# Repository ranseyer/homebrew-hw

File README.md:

View this project on [CADLAB.io](https://cadlab.io/project/22743). 

# homebrew-hw

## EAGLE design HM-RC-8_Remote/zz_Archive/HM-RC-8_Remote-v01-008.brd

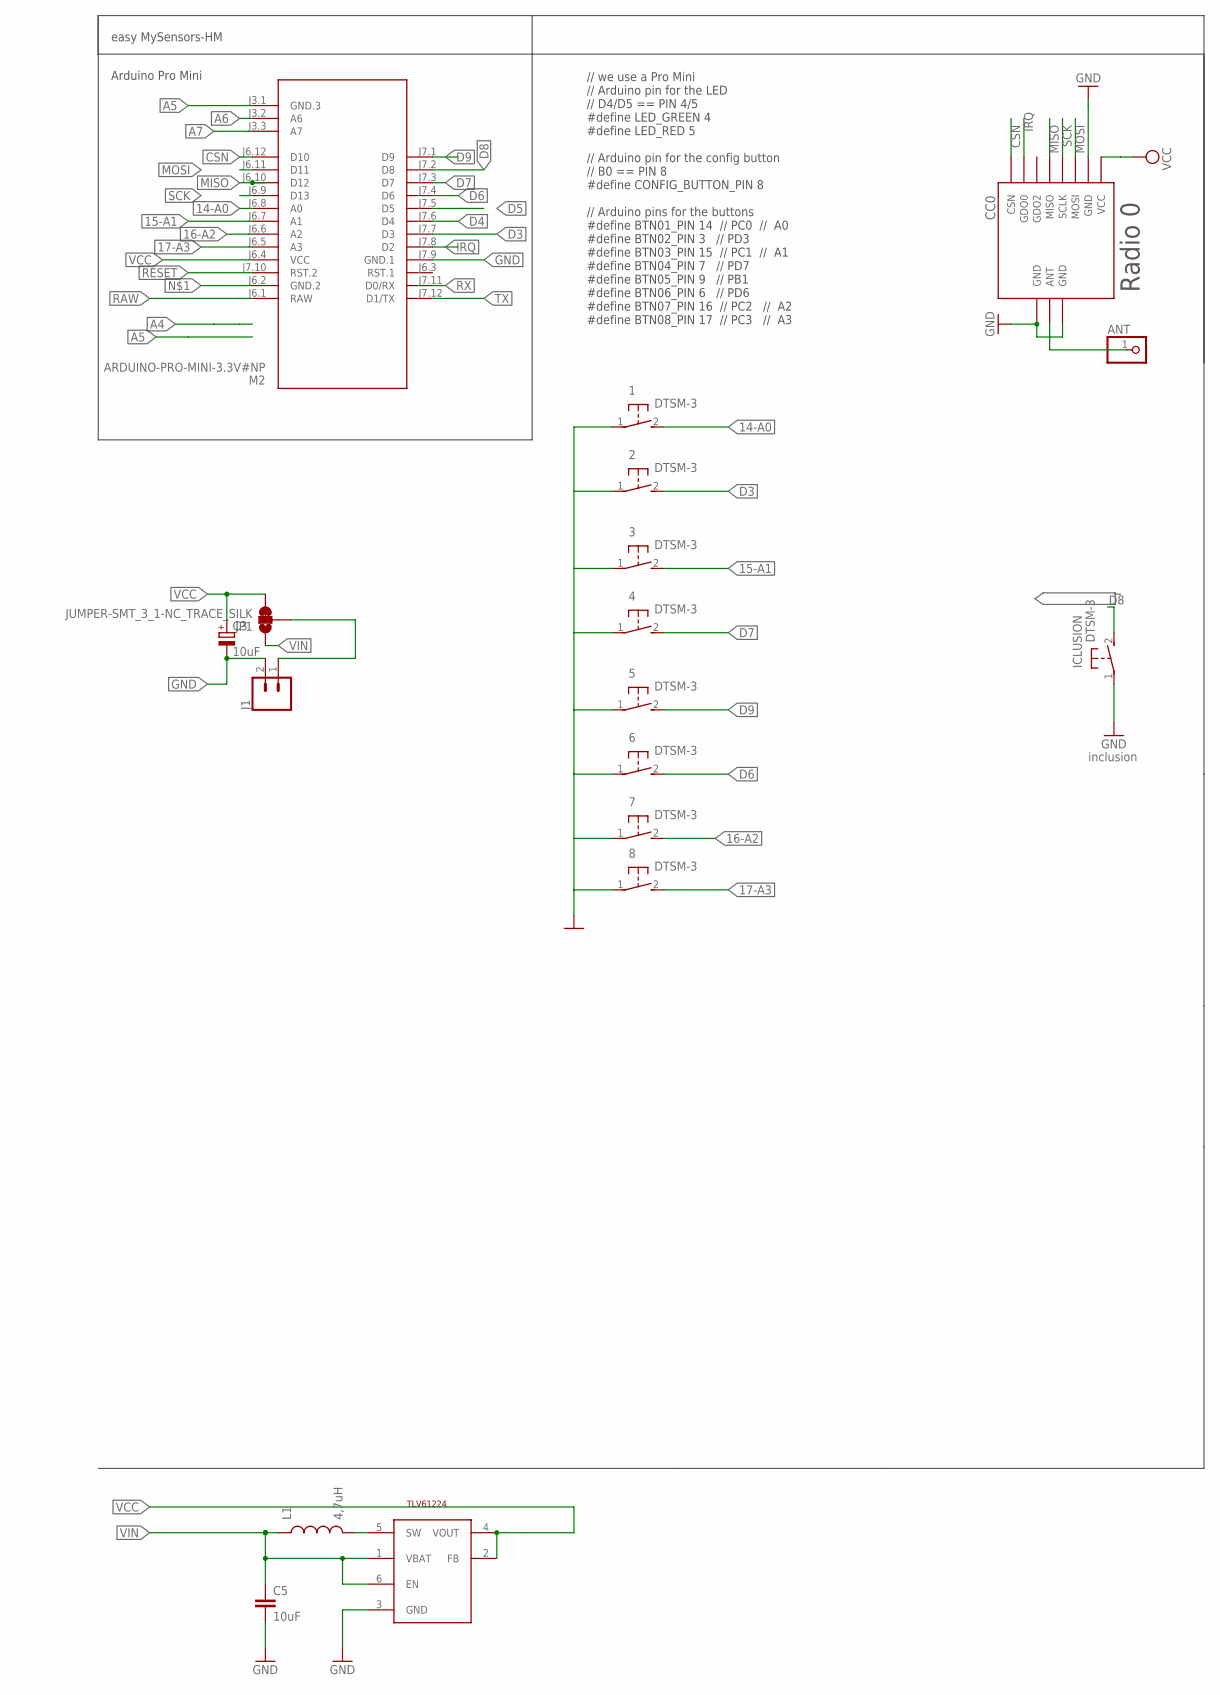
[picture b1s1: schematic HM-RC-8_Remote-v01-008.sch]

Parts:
1, 2, 3, 4, 5, 6, 7, 8: DTSM-3
ANT: PINHD-1X1; 1X01
C3: 10uF; SMC_C
C5: 10uF; 0805
CC0: CC1101; CC1101_MODULE1_SMD
ICLUSION: DTSM-3
J1: CONN_02PTH3; 1X02_LONGPADS
JP1: JUMPER-SMT_3_1-NC_TRACE_SILK; SMT-JUMPER_3_1-NC_TRACE_SILK
L1: 4,7uH; 0805
M2: ARDUINO-PRO-MINI-3.3V#NP; ARDUINO-PRO-MINI#NP
STEPUP: TLV61224; SOT23-6L

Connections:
14-A0: 1.2, M2.J6.8 (A0)
15-A1: 3.2, M2.J6.7 (A1)
16-A2: 7.2, M2.J6.6 (A2)
17-A3: 8.2, M2.J6.5 (A3)
A5: M2.J3.1 (GND.3)
A6: M2.J3.2 (A6)
A7: M2.J3.3 (A7)
ANT0: ANT.1, CC0.ANT
CSN: CC0.CSN, M2.J6.12 (D10)
D3: 2.2, M2.J7.7 (D3)
D4: M2.J7.6 (D4)
D5: M2.J7.5 (D5)
D6: 6.2, M2.J7.4 (D6)
D7: 4.2, M2.J7.3 (D7)
D8: ICLUSION.2, M2.J7.2 (D8)
D9: 5.2, M2.J7.1 (D9)
GND: 1.1, 3.1, 4.1, 5.1, 6.1, 7.1, 8.1, C3.-, C5.2, CC0.GND@0 (GND), CC0.GND@1 (GND), CC0.GND@2 (GND), ICLUSION.1, J1.2, M2.J7.9 (GND.1), STEPUP.3 (GND)
IRQ: CC0.GDO0, M2.J7.8 (D2)
MISO: CC0.MISO, M2.J6.10 (D12)
MOSI: CC0.MOSI, M2.J6.11 (D11)
unnamed: J1.1, JP1.2
unnamed: L1.2, STEPUP.5 (SW)
RAW: M2.J6.1 (RAW)
RESET: M2.J7.10 (RST.2)
RX: M2.J7.11 (D0/RX)
SCK: CC0.SCLK, M2.J6.9 (D13)
TX: M2.J7.12 (D1/TX)
VCC: C3.+, CC0.VCC, JP1.3, M2.J6.4 (VCC), STEPUP.2 (FB), STEPUP.4 (VOUT)
VIN: C5.1, JP1.1, L1.1, STEPUP.1 (VBAT), STEPUP.6 (EN)

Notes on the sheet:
easy MySensors-HM
Arduino Pro Mini
Radio 0
inclusion
// we use a Pro Mini // Arduino pin for the LED // D4/D5 == PIN 4/5 #define LED_GREEN 4 #define LED_RED 5 // Arduino pin for the config button // B0 == PIN 8 #define CONFIG_BUTTON_PIN 8 // Arduino pins for the buttons #define BTN01_PIN 14 // PC0 // A0 #define BTN02_PIN 3 // PD3 #define BTN03_PIN 15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

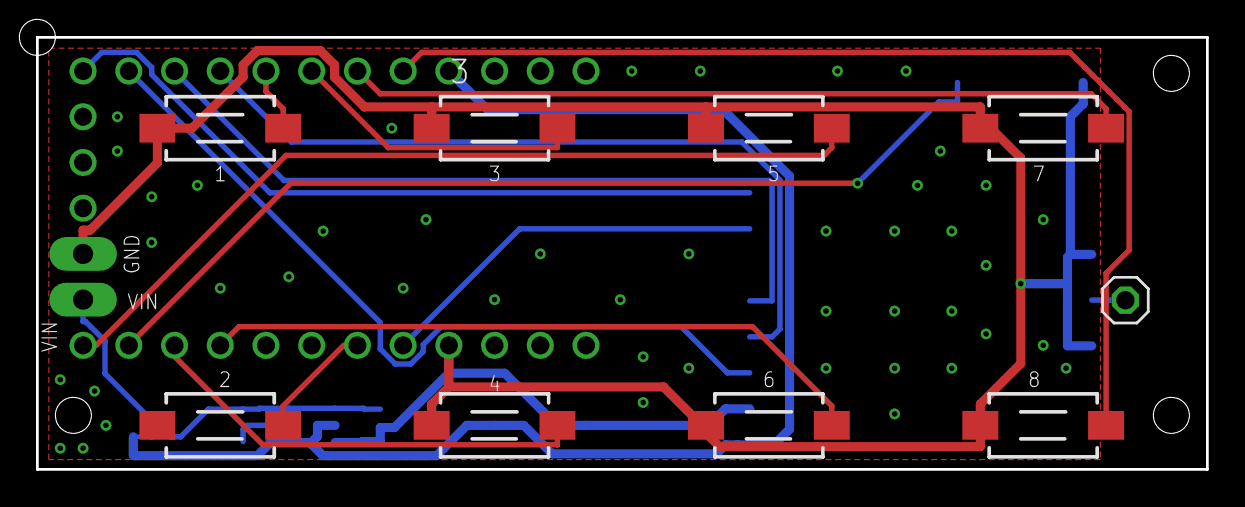
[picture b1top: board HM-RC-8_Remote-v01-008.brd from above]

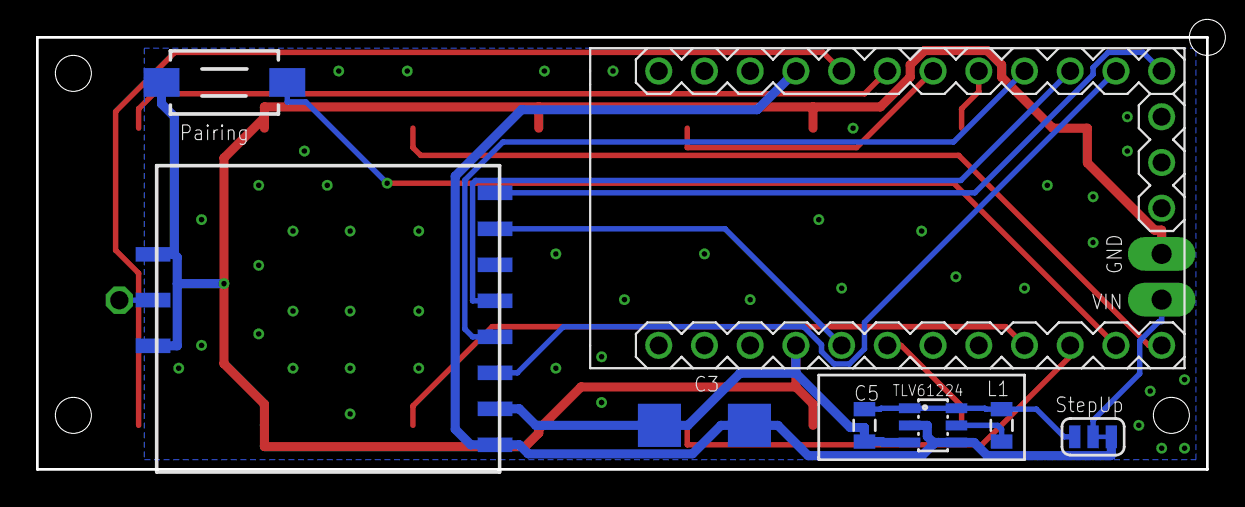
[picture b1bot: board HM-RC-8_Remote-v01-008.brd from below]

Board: 2 copper layers, 65.0 x 24.0 mm, 18 parts (8 on the bottom side), 20 nets.

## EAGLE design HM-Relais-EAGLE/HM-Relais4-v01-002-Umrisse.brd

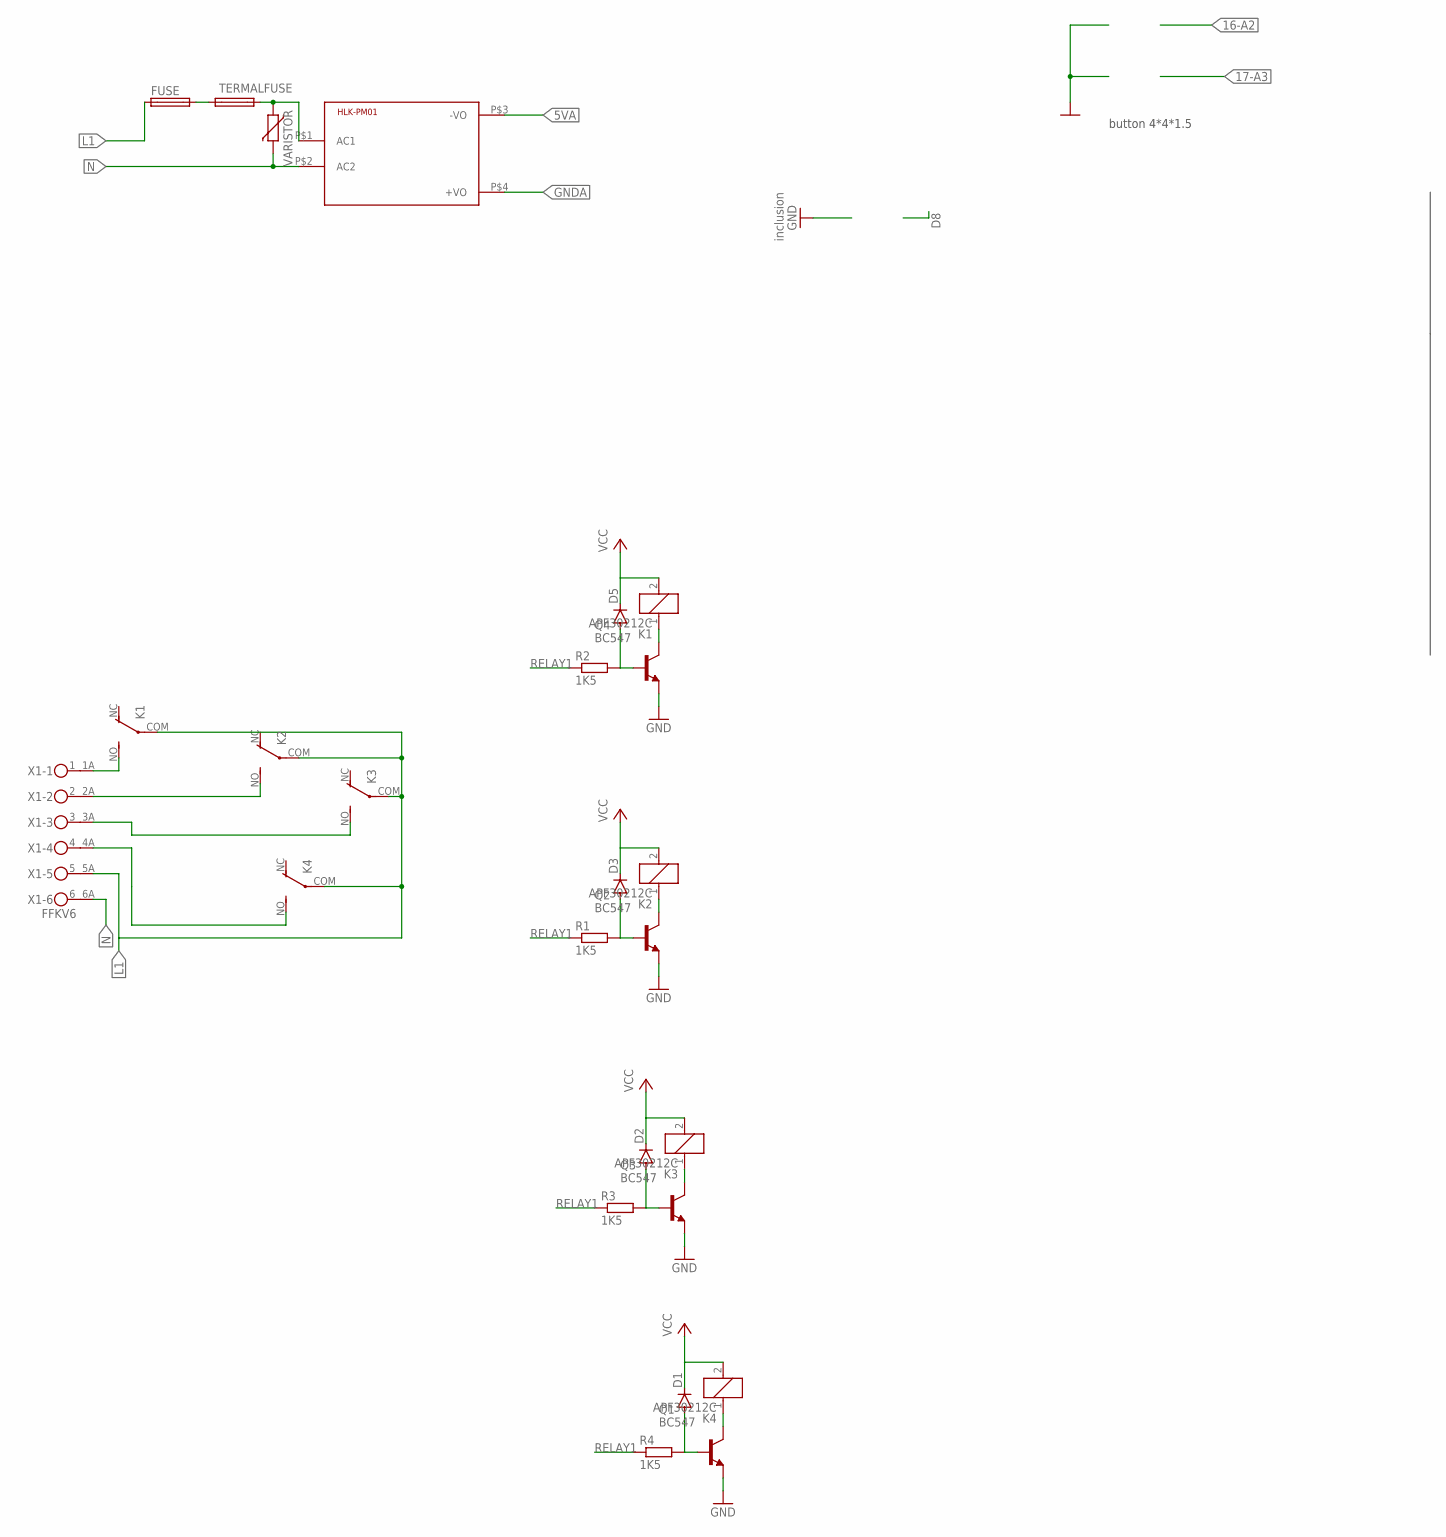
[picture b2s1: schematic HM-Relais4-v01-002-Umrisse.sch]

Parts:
D1, D2, D3, D5: DIODE-D-2.5; D-2.5
FUSE: FUSETE5; TE5
HLK-PM01: HKLPM01
K1, K2, K3, K4: APF30212C
Q1, Q2, Q3, Q4: BC547; TO92
R1, R2, R3, R4: 1K5; 0207/2V
TERMALFUSE: FUSETE5; TE5
VARISTOR: VARISTOR-7,5; R-7,5
X1: FFKV6

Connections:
5VA: HLK-PM01.P$3 (-VO)
GND: Q1.1 (E), Q2.1 (E), Q3.1 (E), Q4.1 (E)
GNDA: HLK-PM01.P$4 (+VO)
L1: FUSE.1, K1.COM, K2.COM, K3.COM, K4.COM, X1.5A (2)
N: HLK-PM01.P$2 (AC2), VARISTOR.2, X1.6A (2)
unnamed: FUSE.2, TERMALFUSE.2
unnamed: K2.1, Q2.3 (C)
unnamed: D3.A, Q2.2 (B), R1.2
unnamed: K3.1, Q3.3 (C)
unnamed: D2.A, Q3.2 (B), R3.2
unnamed: HLK-PM01.P$1 (AC1), TERMALFUSE.1, VARISTOR.1
unnamed: K4.1, Q1.3 (C)
unnamed: D1.A, Q1.2 (B), R4.2
unnamed: K1.NO (S), X1.1A (2)
unnamed: K2.NO (S), X1.2A (2)
unnamed: K3.NO (S), X1.3A (2)
unnamed: K1.1, Q4.3 (C)
unnamed: K4.NO (S), X1.4A (2)
unnamed: D5.A, Q4.2 (B), R2.2
RELAY1: R1.1, R2.1, R3.1, R4.1
VCC: D1.C, D2.C, D3.C, D5.C, K1.2, K2.2, K3.2, K4.2

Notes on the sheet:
inclusion
button 4*4*1.5

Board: 2 copper layers, 21 parts (0 on the bottom side), 19 nets, no tracks yet.

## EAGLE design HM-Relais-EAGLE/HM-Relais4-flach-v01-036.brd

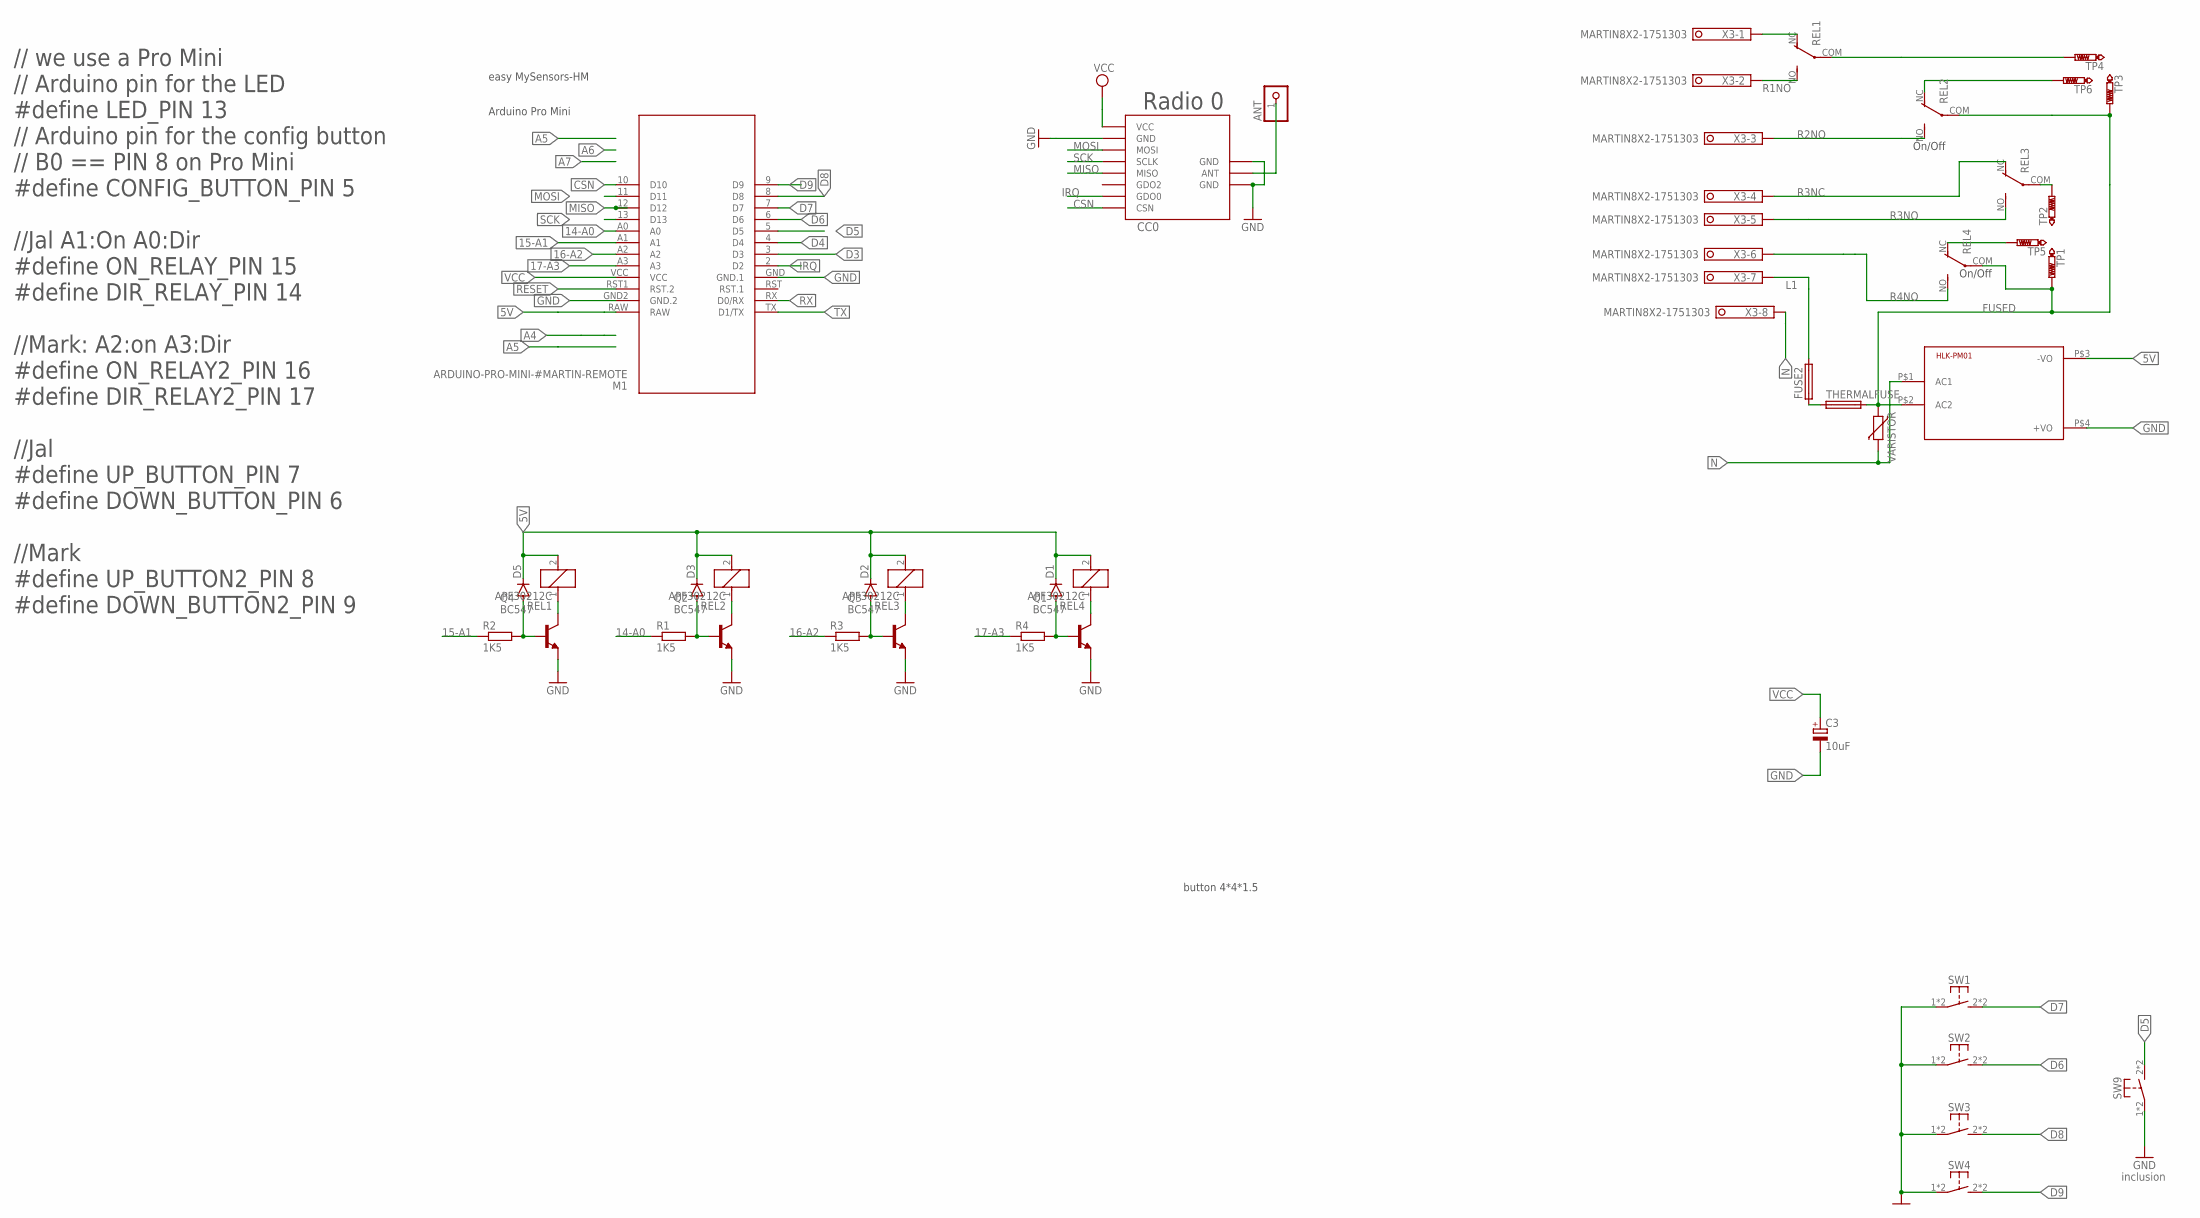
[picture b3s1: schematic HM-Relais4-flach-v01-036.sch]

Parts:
ANT: PINHD-1X1; 1X01
C3: 10uF; SMC_C
CC0: CC1101; CC1101_MODULE1_SMD
D1, D2, D3, D5: DIODE-D-2.5; D-2.5
FUSE2: FUSETE5; TE5
HLK-PM01: HKLPM01
M1: ARDUINO-PRO-MINI-#MARTIN-REMOTE; ARDUINO-PRO-MINI#NP-MARTIN-REMOTE
Q1, Q2, Q3, Q4: BC547; TO92
R1, R2, R3, R4: 1K5; 0207/2V
REL1, REL2, REL3, REL4: APF30212C
SW1, SW2, SW3, SW4, SW9: SW-TACTILE-TL3305; TL3305
THERMALFUSE: FUSETE5; TE5
TP1, TP2, TP3, TP4, TP5, TP6: PTR1TP11SQ; TP11SQ
VARISTOR: VARISTOR-7,5; R-7,5
X3: MARTIN8X2-1751303; 1751303

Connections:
5V: D1.C, D2.C, D3.C, D5.C, HLK-PM01.P$3 (-VO), M1.RAW, REL1.2, REL2.2, REL3.2, REL4.2
14-A0: M1.A0, R1.1
15-A1: M1.A1, R2.1
16-A2: M1.A2, R3.1
17-A3: M1.A3, R4.1
ANT0: ANT.1, CC0.ANT
CSN: CC0.CSN, M1.10 (D10)
D3: M1.3 (D3)
D4: M1.4 (D4)
D5: M1.5 (D5), SW9.2 (S1), SW9.3 (S1)
D6: M1.6 (D6), SW2.2 (S1), SW2.3 (S1)
D7: M1.7 (D7), SW1.2 (S1), SW1.3 (S1)
D8: M1.8 (D8), SW3.2 (S1), SW3.3 (S1)
D9: M1.9 (D9), SW4.2 (S1), SW4.3 (S1)
FUSED: HLK-PM01.P$2 (AC2), REL2.COM, REL4.COM, THERMALFUSE.2, TP1.TP, TP3.TP, VARISTOR.1
GND: C3.-, CC0.GND@0 (GND), CC0.GND@1 (GND), CC0.GND@2 (GND), HLK-PM01.P$4 (+VO), M1.GND (GND.1), M1.GND2 (GND.2), Q1.1 (E), Q2.1 (E), Q3.1 (E), Q4.1 (E), SW1.1, SW1.4 (P1), SW2.1, SW2.4 (P1), SW3.1, SW3.4 (P1), SW4.1, SW4.4 (P1), SW9.1, SW9.4 (P1)
IRQ: CC0.GDO0, M1.2 (D2)
L1: FUSE2.2, X3.15
MISO: CC0.MISO, M1.12 (D12)
MOSI: CC0.MOSI, M1.11 (D11)
N: HLK-PM01.P$1 (AC1), VARISTOR.2, X3.16
unnamed: FUSE2.1, THERMALFUSE.1
unnamed: Q2.3 (C), REL2.1
unnamed: D3.A, Q2.2 (B), R1.2
unnamed: REL3.COM, TP2.TP
unnamed: Q3.3 (C), REL3.1
unnamed: D2.A, Q3.2 (B), R3.2
unnamed: REL4.NC (O), TP5.TP
unnamed: Q1.3 (C), REL4.1
unnamed: D1.A, Q1.2 (B), R4.2
unnamed: REL1.COM, TP4.TP
unnamed: REL2.NC (O), TP6.TP
unnamed: Q4.3 (C), REL1.1
unnamed: D5.A, Q4.2 (B), R2.2
R1NC: REL1.NC (O), X3.9
R1NO: REL1.NO (S), X3.10
R2NO: REL2.NO (S), X3.11
R3NC: REL3.NC (O), X3.12
R3NO: REL3.NO (S), X3.13
R4NO: REL4.NO (S), X3.14
RESET: M1.RST1 (RST.2)
RX: M1.RX (D0/RX)
SCK: CC0.SCLK, M1.13 (D13)
TX: M1.TX (D1/TX)
VCC: C3.+, CC0.VCC, M1.VCC

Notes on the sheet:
easy MySensors-HM
Arduino Pro Mini
Radio 0
inclusion
button 4*4*1.5
// we use a Pro Mini // Arduino pin for the LED #define LED_PIN 13 // Arduino pin for the config button // B0 == PIN 8 on Pro Mini #define CONFIG_BUTTON_PIN 5 //Jal A1:On A0:Dir #define ON_RELAY_PIN 15 #define DIR_RELAY_PIN 14 //Mark: A2:on A3:Dir #define ON_RELAY2_PIN 16 #define DIR_RELAY2_PIN 17 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
On/Off

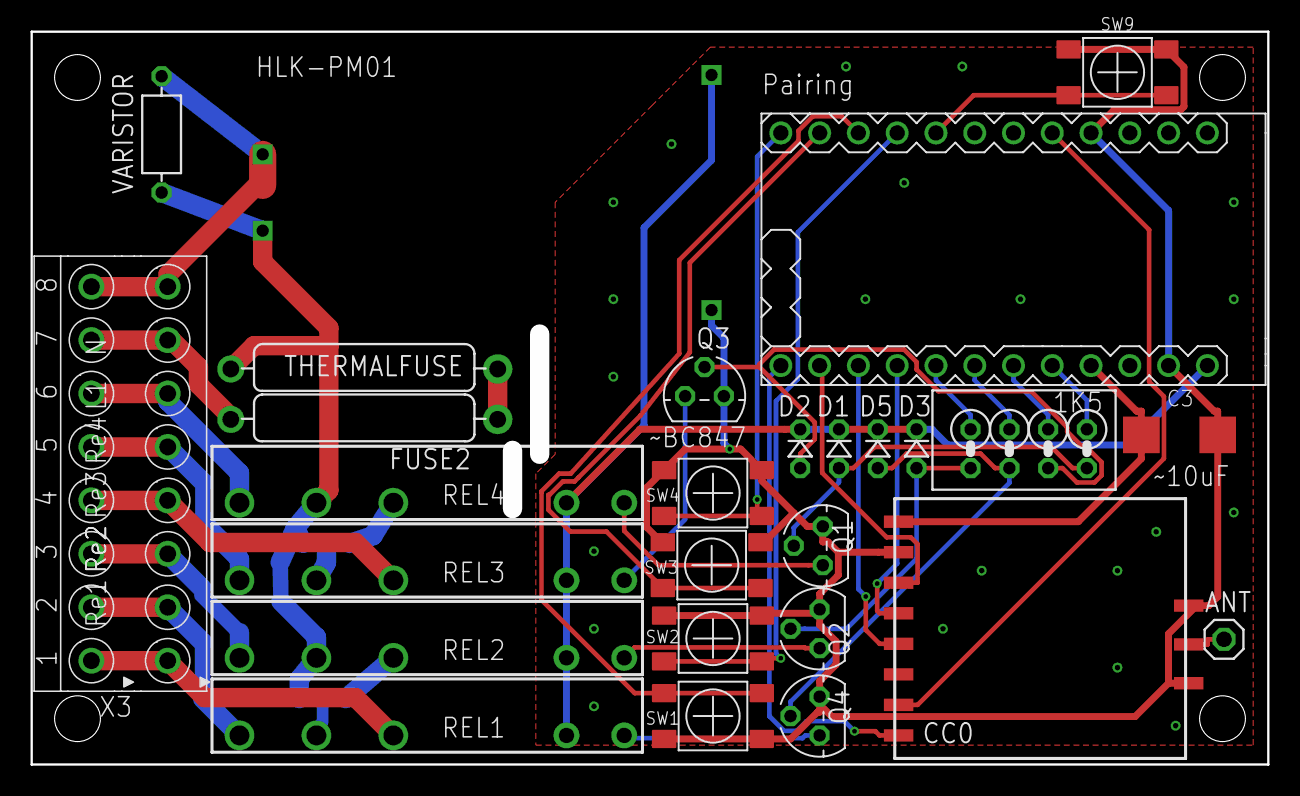
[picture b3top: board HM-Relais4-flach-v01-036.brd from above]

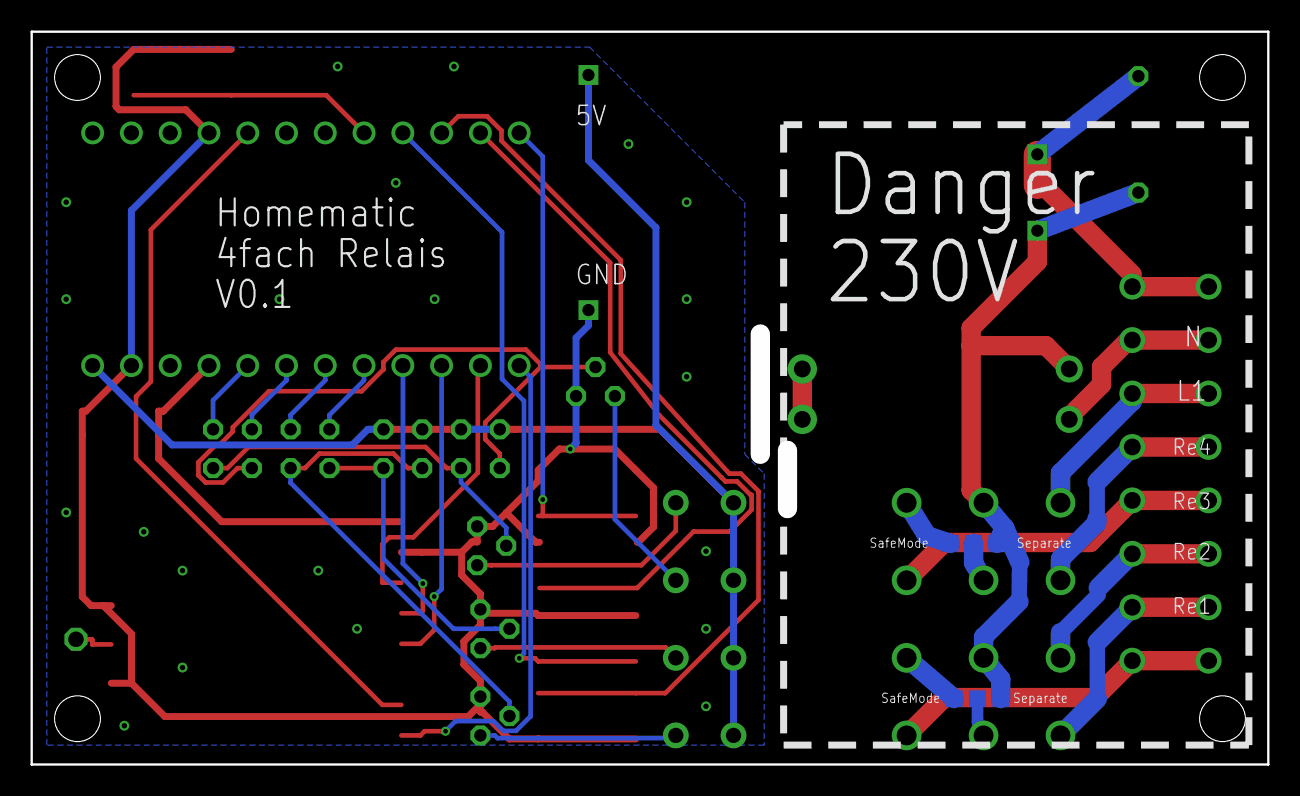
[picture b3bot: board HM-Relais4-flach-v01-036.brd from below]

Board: 2 copper layers, 79.9 x 46.9 mm, 36 parts (6 on the bottom side), 40 nets.

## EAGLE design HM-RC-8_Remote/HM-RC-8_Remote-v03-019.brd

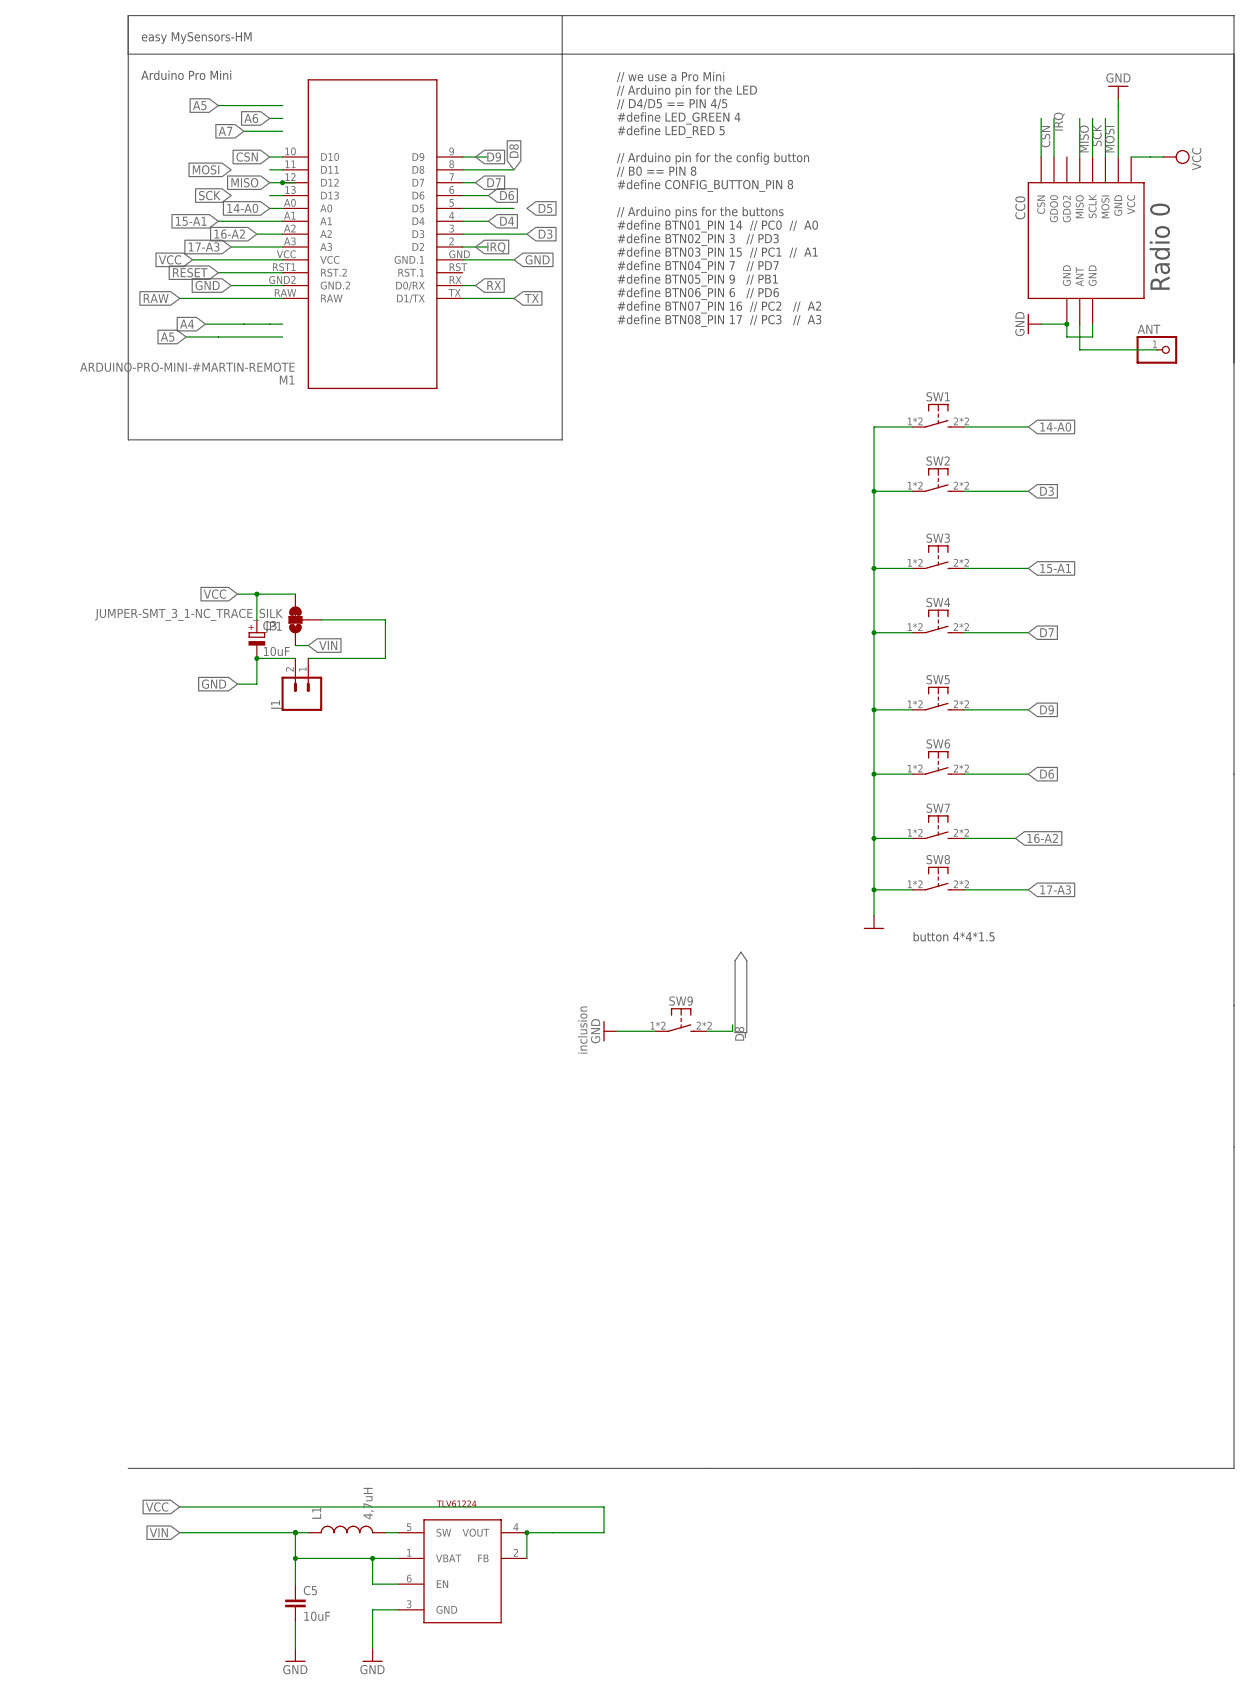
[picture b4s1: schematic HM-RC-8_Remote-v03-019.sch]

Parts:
ANT: PINHD-1X1; 1X01
C3: 10uF; SMC_C
C5: 10uF; 0805
CC0: CC1101; CC1101_MODULE1_SMD
J1: CONN_02PTH3; 1X02_LONGPADS
JP1: JUMPER-SMT_3_1-NC_TRACE_SILK; SMT-JUMPER_3_1-NC_TRACE_SILK
L1: 4,7uH; 0805
M1: ARDUINO-PRO-MINI-#MARTIN-REMOTE; ARDUINO-PRO-MINI#NP-MARTIN-REMOTE
STEPUP: TLV61224; SOT23-6L
SW1, SW2, SW3, SW4, SW5, SW6, SW7, SW8, SW9: SW-TACTILE-TL3305; TL3305

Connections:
14-A0: M1.A0, SW1.2 (S1), SW1.3 (S1)
15-A1: M1.A1, SW3.2 (S1), SW3.3 (S1)
16-A2: M1.A2, SW7.2 (S1), SW7.3 (S1)
17-A3: M1.A3, SW8.2 (S1), SW8.3 (S1)
ANT0: ANT.1, CC0.ANT
CSN: CC0.CSN, M1.10 (D10)
D3: M1.3 (D3), SW2.2 (S1), SW2.3 (S1)
D4: M1.4 (D4)
D5: M1.5 (D5)
D6: M1.6 (D6), SW6.2 (S1), SW6.3 (S1)
D7: M1.7 (D7), SW4.2 (S1), SW4.3 (S1)
D8: M1.8 (D8), SW9.2 (S1), SW9.3 (S1)
D9: M1.9 (D9), SW5.2 (S1), SW5.3 (S1)
GND: C3.-, C5.2, CC0.GND@0 (GND), CC0.GND@1 (GND), CC0.GND@2 (GND), J1.2, M1.GND (GND.1), M1.GND2 (GND.2), STEPUP.3 (GND), SW1.1, SW1.4 (P1), SW2.1, SW2.4 (P1), SW3.1, SW3.4 (P1), SW4.1, SW4.4 (P1), SW5.1, SW5.4 (P1), SW6.1, SW6.4 (P1), SW7.1, SW7.4 (P1), SW8.1, SW8.4 (P1), SW9.1, SW9.4 (P1)
IRQ: CC0.GDO0, M1.2 (D2)
MISO: CC0.MISO, M1.12 (D12)
MOSI: CC0.MOSI, M1.11 (D11)
unnamed: J1.1, JP1.2
unnamed: L1.2, STEPUP.5 (SW)
RAW: M1.RAW
RESET: M1.RST1 (RST.2)
RX: M1.RX (D0/RX)
SCK: CC0.SCLK, M1.13 (D13)
TX: M1.TX (D1/TX)
VCC: C3.+, CC0.VCC, JP1.3, M1.VCC, STEPUP.2 (FB), STEPUP.4 (VOUT)
VIN: C5.1, JP1.1, L1.1, STEPUP.1 (VBAT), STEPUP.6 (EN)

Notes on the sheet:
easy MySensors-HM
Arduino Pro Mini
Radio 0
inclusion
// we use a Pro Mini // Arduino pin for the LED // D4/D5 == PIN 4/5 #define LED_GREEN 4 #define LED_RED 5 // Arduino pin for the config button // B0 == PIN 8 #define CONFIG_BUTTON_PIN 8 // Arduino pins for the buttons #define BTN01_PIN 14 // PC0 // A0 #define BTN02_PIN 3 // PD3 #define BTN03_PIN 15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
button 4*4*1.5

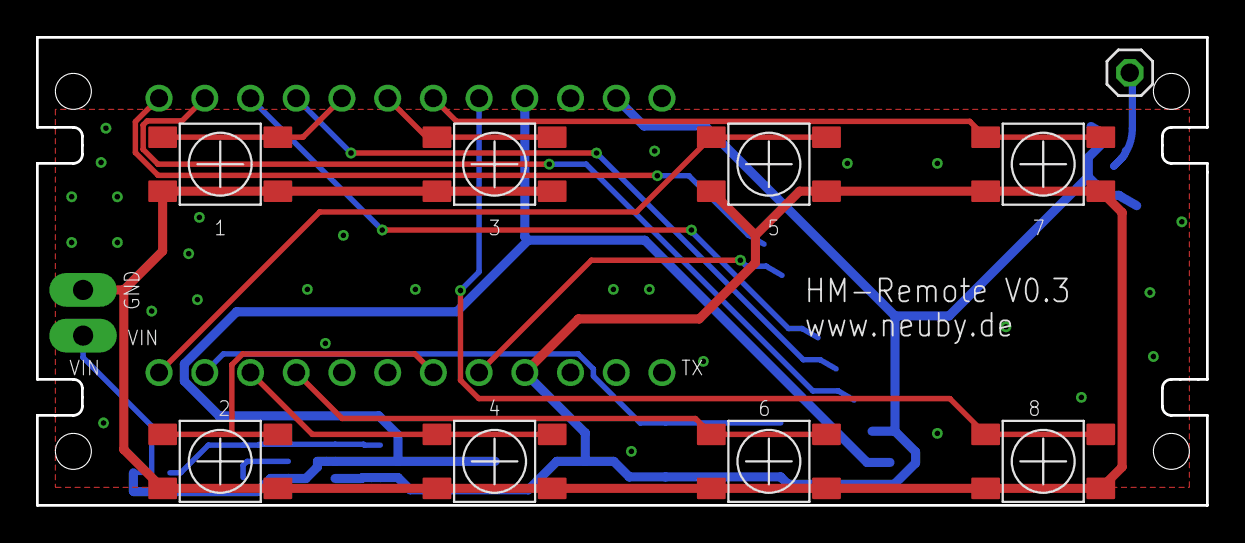
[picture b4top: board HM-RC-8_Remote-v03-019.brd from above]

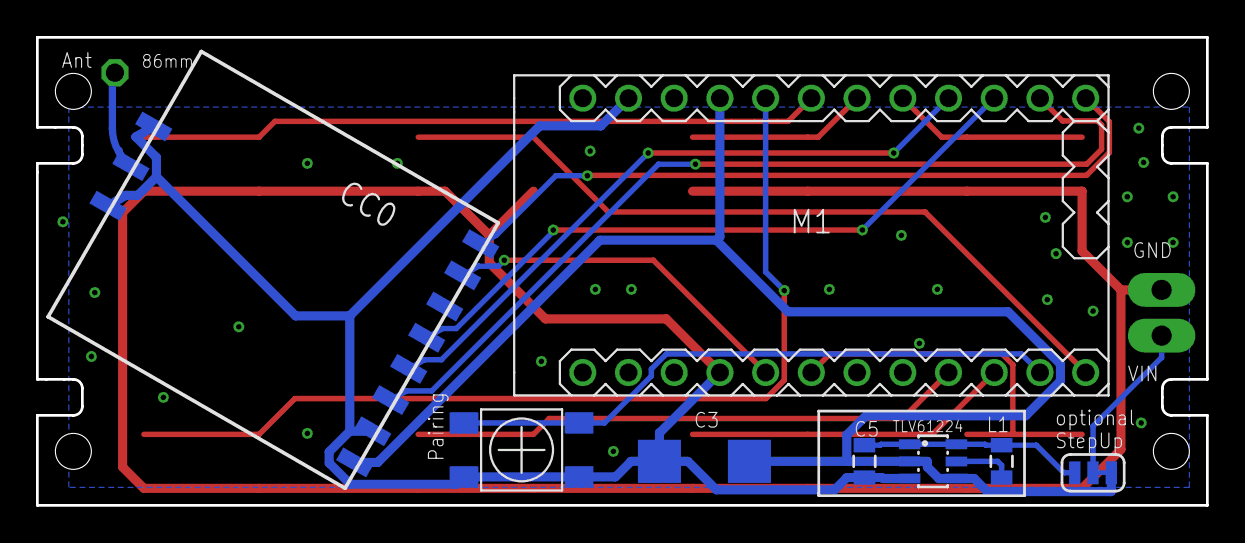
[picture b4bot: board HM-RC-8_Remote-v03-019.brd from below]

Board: 2 copper layers, 65.0 x 26.0 mm, 18 parts (8 on the bottom side), 20 nets.

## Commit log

2019-06-04 RC-8
2019-06-06 Remote
2019-08-03 Doku
2019-10-26 V03, Pics
2019-12-29 docs
2020-01-12 HM Relais
2020-02-07 Relais
2020-04-01 Backlink to CADLAB.io has been added.
2020-06-28 Sketch
2021-04-12 Moved Homematic projects

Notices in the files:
parts and their libraries:
SparkFun-Passives: Licensing: CC v3.0 Share-Alike You are welcome to use this library for commercial purposes.
SparkFun-Connectors: Licensing: Creative Commons ShareAlike 4.0 International - https://creativecommons.org/licenses/by-sa/4.0
